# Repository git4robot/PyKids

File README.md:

# PyKids
Python Learning for kids

1, Eratosthenes筛法（Sieve of Eratosthenes） & 欧拉线性筛法（Sieve of Euler）
   Eratosthenes筛法可能对同一个质数筛去多次
   欧拉线性筛法,因为任何合数都能表示成一系列素数的积,规定每个合数只用其最小的一个质因数去筛
   欧拉函数：在数论中，对正整数n，欧拉函数是少于或等于n的数中与n互质的数的数目。

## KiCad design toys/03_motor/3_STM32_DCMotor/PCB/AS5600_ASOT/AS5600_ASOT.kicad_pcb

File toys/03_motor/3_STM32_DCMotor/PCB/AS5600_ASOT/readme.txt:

Ref:
https://www.tindie.com/products/nsted/mocoder-as5600-magnetic-encoder/

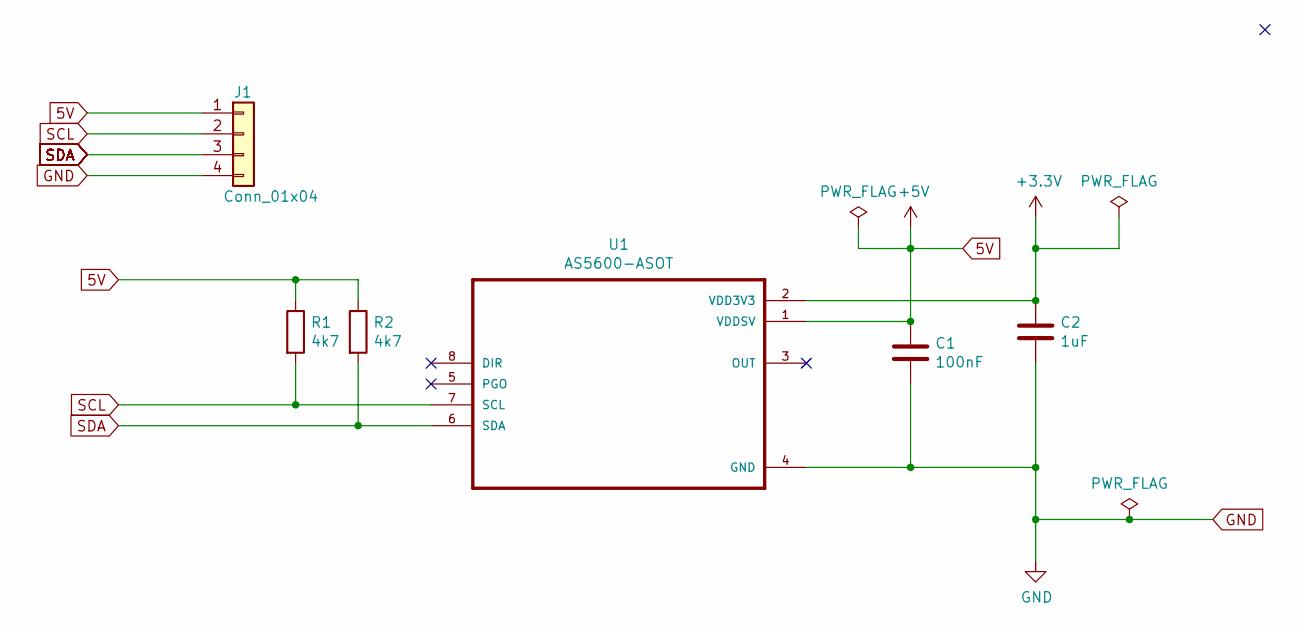
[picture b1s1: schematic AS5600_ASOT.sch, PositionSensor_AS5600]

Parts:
C1: 100nF; C_1206_3216Metric_Pad1.42x1.75mm_HandSolder
C2: 1uF; C_1206_3216Metric_Pad1.42x1.75mm_HandSolder
J1: Conn_01x04; JST_SH_BM04B-SRSS-TB_1x04-1MP_P1.00mm_Vertical
R1, R2: 4k7; R_1206_3216Metric_Pad1.42x1.75mm_HandSolder
U1: AS5600-ASOT; SOIC-8_3.9x4.9mm_P1.27mm

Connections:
5V: C1.1, J1.1, R1.1, R2.1, U1.1 (VDDSV)
+3V3: C2.1, U1.2 (VDD3V3)
GND: C1.2, C2.2, J1.4, U1.4 (GND)
SCL: J1.2, R1.2, U1.7 (SCL)
SDA: J1.3, R2.2, U1.6 (SDA)

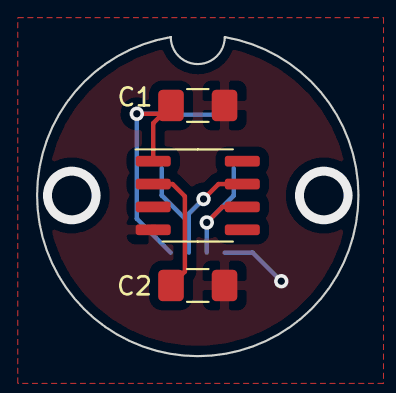
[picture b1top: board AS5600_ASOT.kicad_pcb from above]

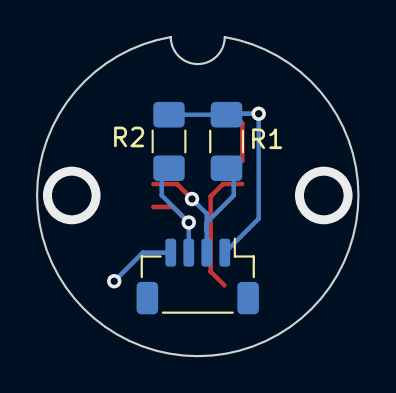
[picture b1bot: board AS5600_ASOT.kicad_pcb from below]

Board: 2 copper layers, 17.9 x 17.7 mm, 6 parts (3 on the bottom side), 5 nets.

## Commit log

2020-02-20 Rename import_turtleTk_class.py to kernel 文件/import_turtleTk_class.py
2020-02-20 Rename kernel 文件/import_turtleTk_class.py to kernel 文件/module 文件/import_turtleTk_class.py
